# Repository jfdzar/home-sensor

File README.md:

# home-sensor
Home Multi Sensor created based on ESP8266 to work with Homeassistant and ESP-Home

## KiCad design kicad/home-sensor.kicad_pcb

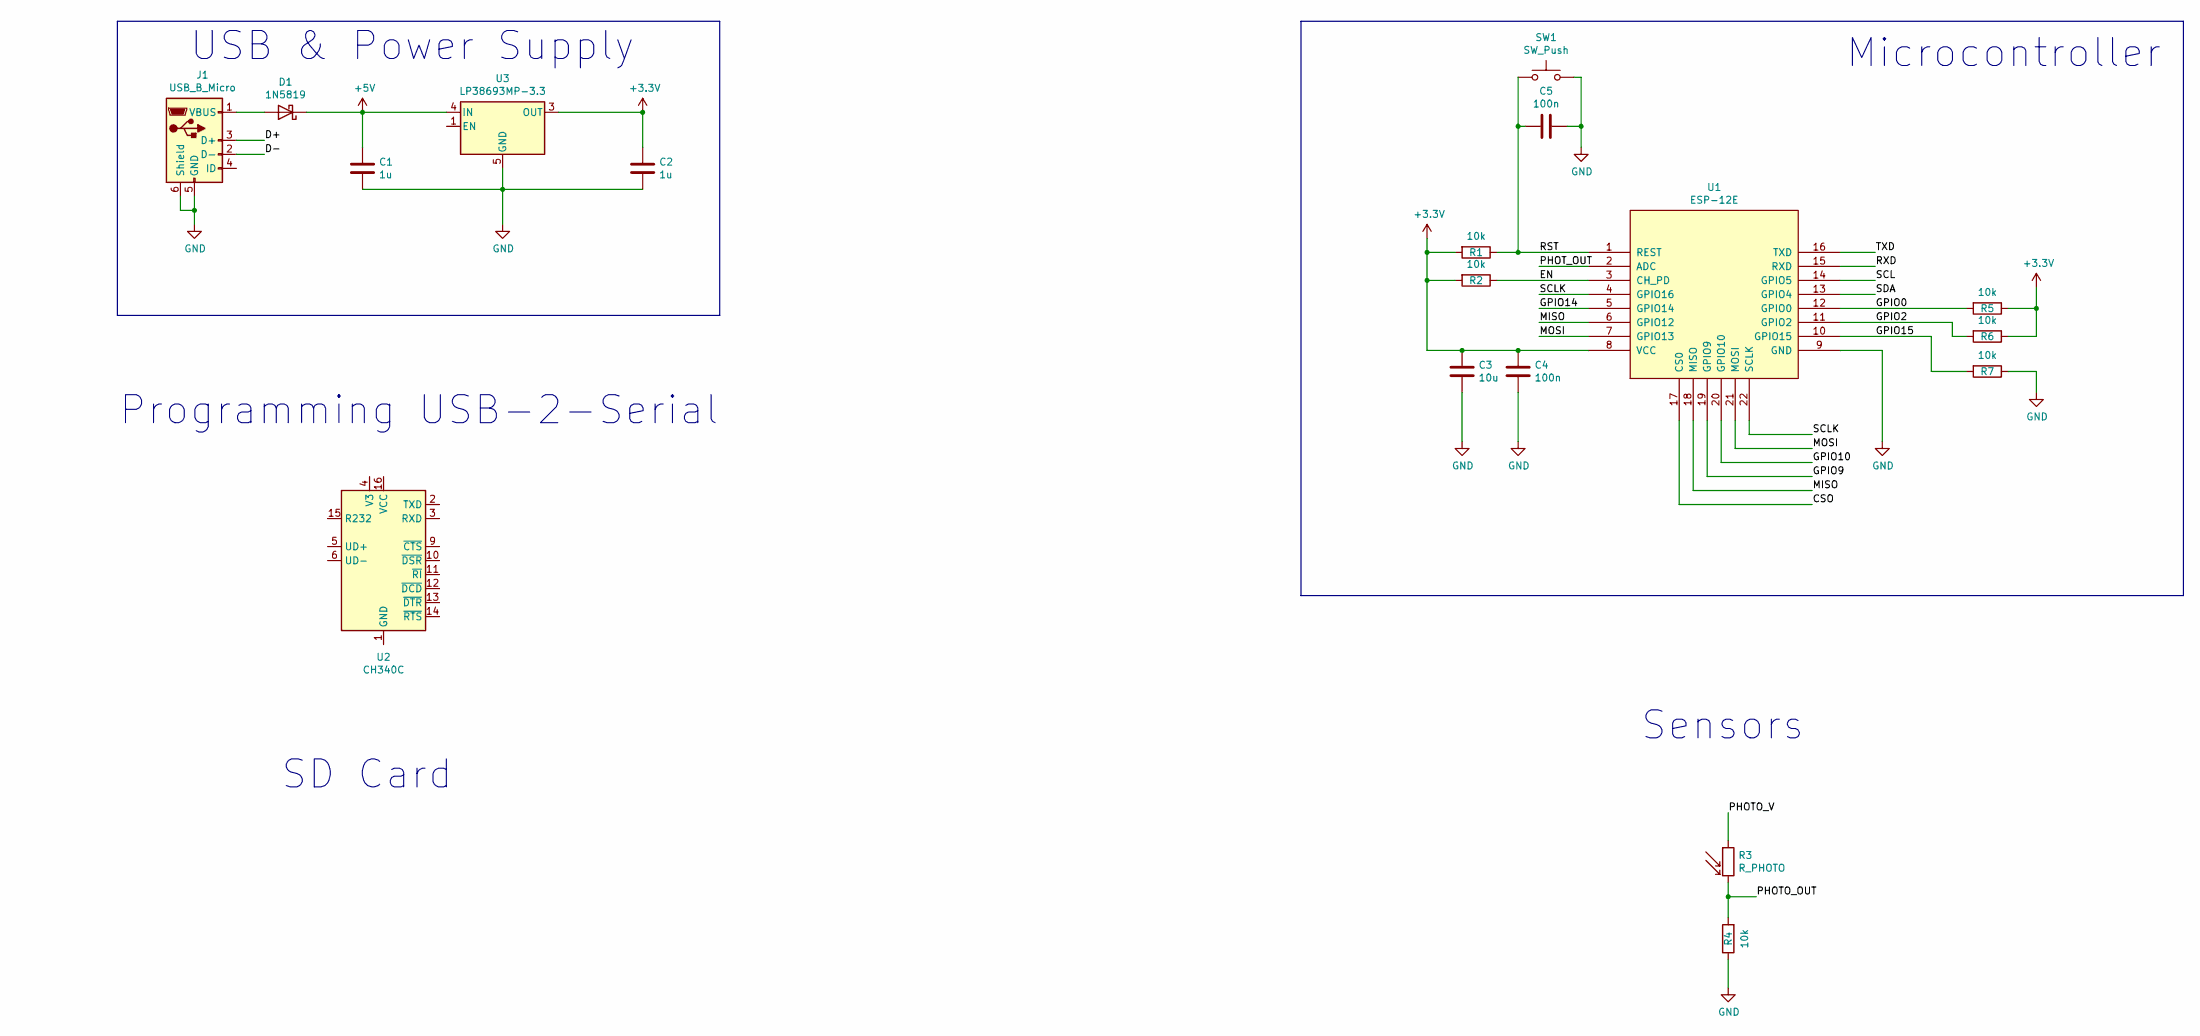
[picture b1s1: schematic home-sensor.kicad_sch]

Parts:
C1, C2: 1u; C_0603_1608Metric
C3: 10u; C_0603_1608Metric
C4, C5: 100n; C_0603_1608Metric
D1: 1N5819; D_DO-41_SOD81_P10.16mm_Horizontal
J1: USB_B_Micro; USB_Micro-AB_Molex_47590-0001
R1, R2, R4, R5, R6, R7: 10k; R_0603_1608Metric
R3: R_PHOTO; R_0603_1608Metric
SW1: SW_Push; SW_SPST_B3S-1000
U1: ESP-12E
U2: CH340C; SOIC-16_3.9x9.9mm_P1.27mm
U3: LP38693MP-3.3; SOT-223-5

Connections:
+3V3: C2.1, C3.1, C4.1, R1.2, R2.2, R5.1, R6.1, U1.8 (VCC), U3.3 (OUT)
+5V: C1.1, D1.1 (K), U3.4 (IN)
/CSO: U1.17 (CS0)
/D+: J1.3 (D+)
/D-: J1.2 (D-)
/EN: R2.1, U1.3 (CH_PD)
/GPIO0: R5.2, U1.12 (GPIO0)
/GPIO2: R6.2, U1.11 (GPIO2)
/GPIO9: U1.19 (GPIO9)
/GPIO10: U1.20 (GPIO10)
/GPIO14: U1.5 (GPIO14)
/GPIO15: R7.2, U1.10 (GPIO15)
/MISO: U1.6 (GPIO12), U1.18 (MISO)
/MOSI: U1.7 (GPIO13), U1.21 (MOSI)
/PHOTO_OUT: R3.2, R4.2
/PHOTO_V: R3.1
/PHOT_OUT: U1.2 (ADC)
/RST: C5.2, R1.1, SW1.1, U1.1 (REST)
/RXD: U1.15 (RXD)
/SCL: U1.14 (GPIO5)
/SCLK: U1.4 (GPIO16), U1.22 (SCLK)
/SDA: U1.13 (GPIO4)
/TXD: U1.16 (TXD)
GND: C1.2, C2.2, C3.2, C4.2, C5.1, J1.5 (GND), J1.6 (Shield), R4.1, R7.1, SW1.2, U1.9 (GND), U3.5 (GND)
unnamed: D1.2 (A), J1.1 (VBUS)

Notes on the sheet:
Microcontroller
Sensors
USB & Power Supply
SD Card
Programming USB-2-Serial

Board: 2 copper layers, 18 parts (0 on the bottom side), 13 nets, no tracks yet.

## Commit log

2021-10-07 Original Commit
2021-10-09 added new components to schematic
2022-01-05 Updated files to Kicad 6.0 and deleted unsude files
